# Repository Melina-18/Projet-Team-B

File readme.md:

# Bienvenue dans 1/3 de projet 

Thème : Réaliser un projet sur un Escape Game 

Objectif : avoir une clé pour passer au projet d'un autre groupe

## Info utile :
Dimension du cube : 30*30 cm  

Rebord de 0,5 cm autour de chaque pièce 

Profondeur de 3 cm

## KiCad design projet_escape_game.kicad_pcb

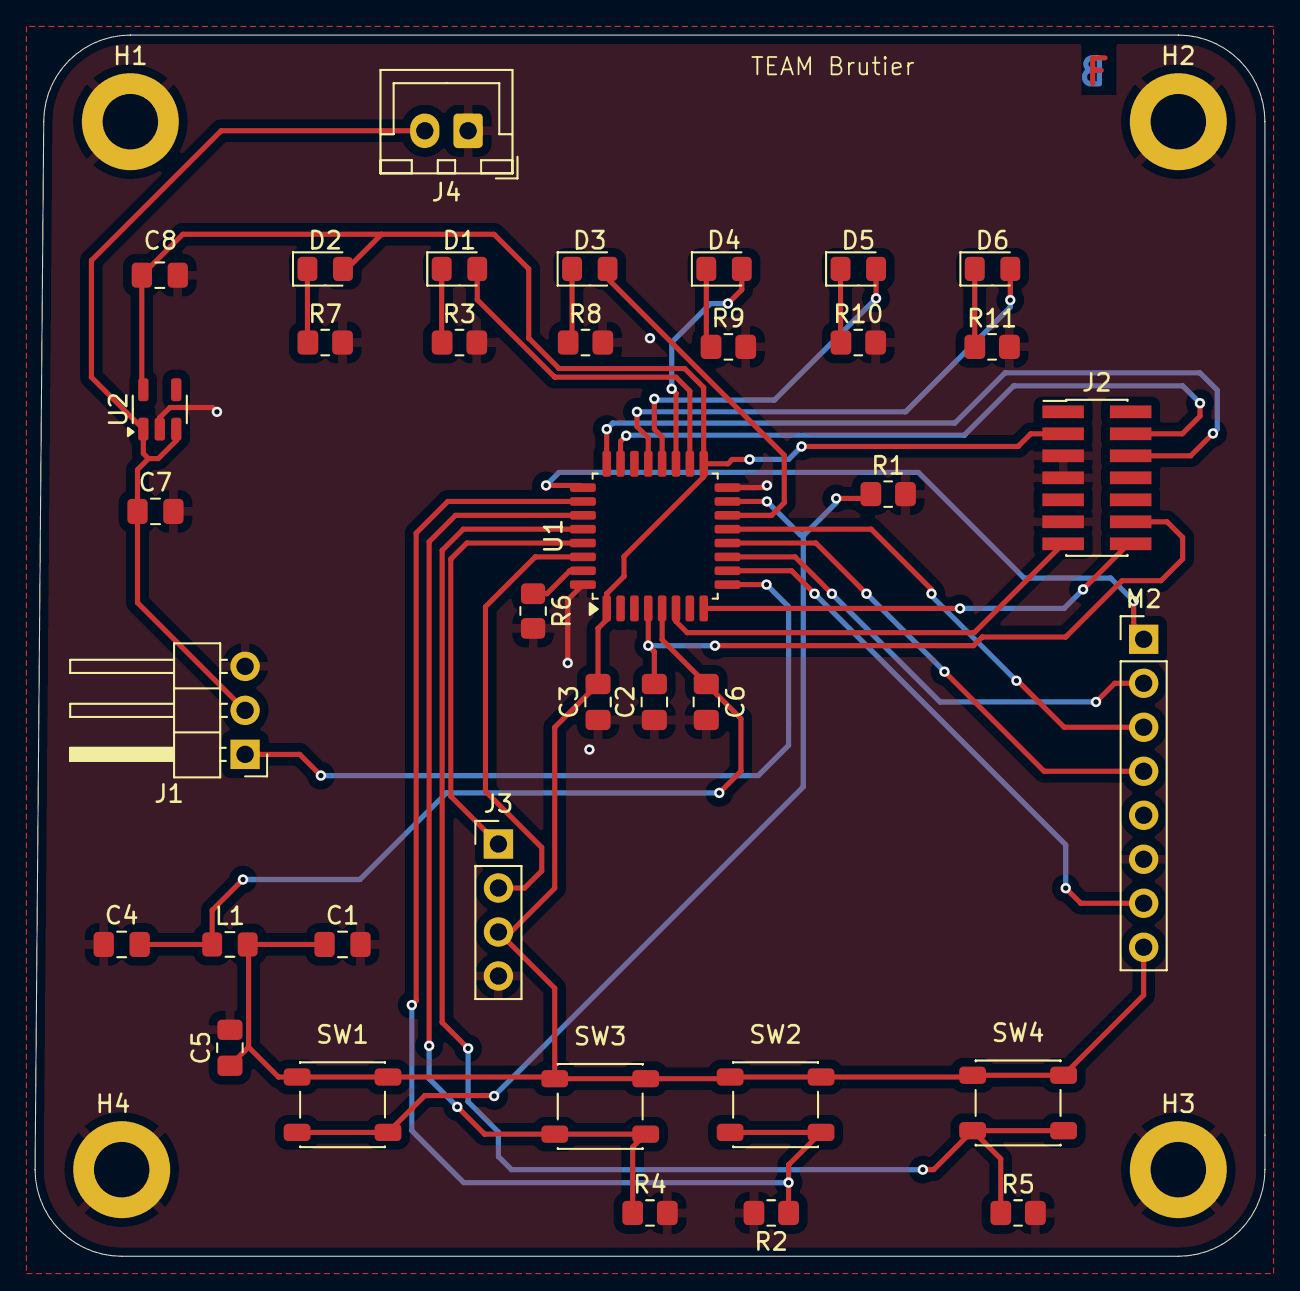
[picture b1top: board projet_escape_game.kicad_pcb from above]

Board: 2 copper layers, 71.0 x 70.5 mm, 41 parts (0 on the bottom side), 33 nets.

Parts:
C1: 4u7; C_0805_2012Metric_Pad1.18x1.45mm_HandSolder
C2, C3, C5: 100n; C_0805_2012Metric_Pad1.18x1.45mm_HandSolder
C4: 1u; C_0805_2012Metric_Pad1.18x1.45mm_HandSolder
C6: 10n; C_0805_2012Metric_Pad1.18x1.45mm_HandSolder
C7, C8: 1uF; C_0805_2012Metric_Pad1.18x1.45mm_HandSolder
D1, D2, D3, D4, D5, D6: LED_Small; LED_0805_2012Metric_Pad1.15x1.40mm_HandSolder
H1, H2, H3, H4: MountingHole_Pad; MountingHole_3.2mm_M3_DIN965_Pad
J1: Conn_01x03_Pin; PinHeader_1x03_P2.54mm_Horizontal
J2: Conn_02x07_Odd_Even; PinHeader_2x07_P1.27mm_Vertical_SMD
J3: Conn_OLED_Display; PinHeader_1x04_P2.54mm_Vertical
J4: Conn_01x02; JST_XH_B2B-XH-A_1x02_P2.50mm_Vertical
L1: 39n; L_0805_2012Metric_Pad1.15x1.40mm_HandSolder
M2: RFID-RC522; PinHeader_1x08_P2.54mm_Vertical
R1, R2, R4, R5: R_Small; R_0805_2012Metric_Pad1.20x1.40mm_HandSolder
R3, R7, R8, R9, R10, R11: 1k; R_0805_2012Metric_Pad1.20x1.40mm_HandSolder
R6: 100k; R_0805_2012Metric_Pad1.20x1.40mm_HandSolder
SW1, SW2, SW3, SW4: SW_SPST; SW_SPST_PTS647_Sx50
U1: STM32L021K4Tx; LQFP-32_7x7mm_P0.8mm
U2: BU33SD5WG-TR; SOT-23-5

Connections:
+3.3V: C1.1, C3.2, C5.1, C8.1, D2.2 (A), J2.3, J3.3, L1.2, M2.8 (3V3), SW1.1 (A), SW2.1 (A), SW3.1 (A), SW4.1 (A), U1.1 (VDD), U1.17 (VDD), U2.5 (VOUT)
+3.3VA: C4.2, C6.1, L1.1, U1.5 (VDDA)
+5V: C7.1, J1.2, J4.2, U2.1 (VIN), U2.3 (~SHDN)
Button1: R1.1, SW1.2 (B), U1.15 (PB1)
Button2: R2.1, SW2.2 (B), U1.26 (PB3)
Button3: R4.1, SW3.2 (B), U1.27 (PB4)
Button4: R5.1, SW4.2 (B), U1.28 (PB5)
DAC_nCS: M2.7 (RST), U1.10 (PA4)
GND: C1.2, C2.1, C3.1, C4.1, C5.2, C6.2, C7.2, C8.2, H1.1, H2.1, H3.1, H4.1, J1.3, J2.5, J2.7, J2.11, J3.4, J4.1, M2.6 (GND), R1.2, R2.2, R3.2, R4.2, R5.2, R6.2, R7.2, R8.2, R9.2, R10.2, R11.2, U1.16 (VSS), U1.32 (VSS), U2.2 (GND)
I2C1_SCL: J3.1, U1.29 (PB6)
I2C1_SDA: J3.2, U1.30 (PB7)
LED1_STATUS: D4.2 (A), U1.19 (PA9)
LED2_STATUS: D5.2 (A), U1.20 (PA10)
LED3_STATUS: D6.2 (A), U1.21 (PA11)
LED_ERROR_STATUS: D3.2 (A), U1.14 (PB0)
LED_STATUS: D1.2 (A), U1.18 (PA8)
NRST: C2.2, J2.12, U1.4 (NRST)
unnamed: D1.1 (K), R3.1
unnamed: D2.1 (K), R7.1
unnamed: D3.1 (K), R8.1
unnamed: D4.1 (K), R9.1
unnamed: D5.1 (K), R10.1
unnamed: D6.1 (K), R11.1
unnamed: R6.1, U1.31 (PB9)
PWM: J1.1, U1.9 (PA3)
SPI1_MISO: M2.4 (MISO), U1.12 (PA6)
SPI1_MOSI: M2.3 (MOSI), U1.13 (PA7)
SPI1_NSS: M2.1 (SDA), U1.25 (PA15)
SPI1_SCK: M2.2 (SCK), U1.11 (PA5)
SWDCK: J2.6, U1.24 (PA14)
SWDIO: J2.4, U1.23 (PA13)
USART2_RX: J2.13, U1.6 (PA0)
USART2_TX: J2.14, U1.8 (PA2)

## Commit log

2025-03-03 Create liste d'achats
2025-03-03 Rename liste d'achats to liste d'achats.md
2025-03-03 Rename Projet Plan de la face (1).png to Plan de la face.png
2025-03-03 Rename Projet Plan de la face.png to Plan de la face.png
2025-03-03 Update histoire.md*
2025-03-10 Rename image.png to PCB.png
2025-04-07 Rename image.png to schématique_PCB.png
2025-04-28 PCB schématique
2025-04-28 Rename image.png to PCB_schématique.png
2025-04-28 Rename Capture d'écran 2025-04-28 162155.png to PCB
2025-05-05 Create Rapport final du projet
2025-05-05 Update Rapport final du projet
2025-05-12 Create Plan 3D face
